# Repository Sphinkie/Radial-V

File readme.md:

# Radial-V

## Présentation

Remise en fonctionnement d'un poste de TSF, avec radio FM, player MP3, et afficheur LCD.

## Fabrication

Plusieurs éléments ont été réalisés: logiciel, circuits électroniques et supports en PLA.

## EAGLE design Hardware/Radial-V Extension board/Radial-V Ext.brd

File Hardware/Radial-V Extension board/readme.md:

# RADIAL-V

## Extension Board

Cette carte regroupe tous les capteurs et actuateurs (boutons, LEDs, etc) du système et les envoie sur une nappe 25 fils vers l'Arduino.

Le circuit intégré 74HC14 est un *trigger de Schmitt inversé* qui, associé aux capacités, supprime les rebonds des boutons poussoirs, et transforme les impulsions en signaux carrés propres inversés (*active high*).  
Les *relais* servent à commuter le signal audio de sortie soit de la source "Carte MP3", soit de la source "Carte radio FM".  
Les composants *grisés* sont des spares non utilisés.

Schémas et PCB compatibles avec le logiciel **Eagle**.

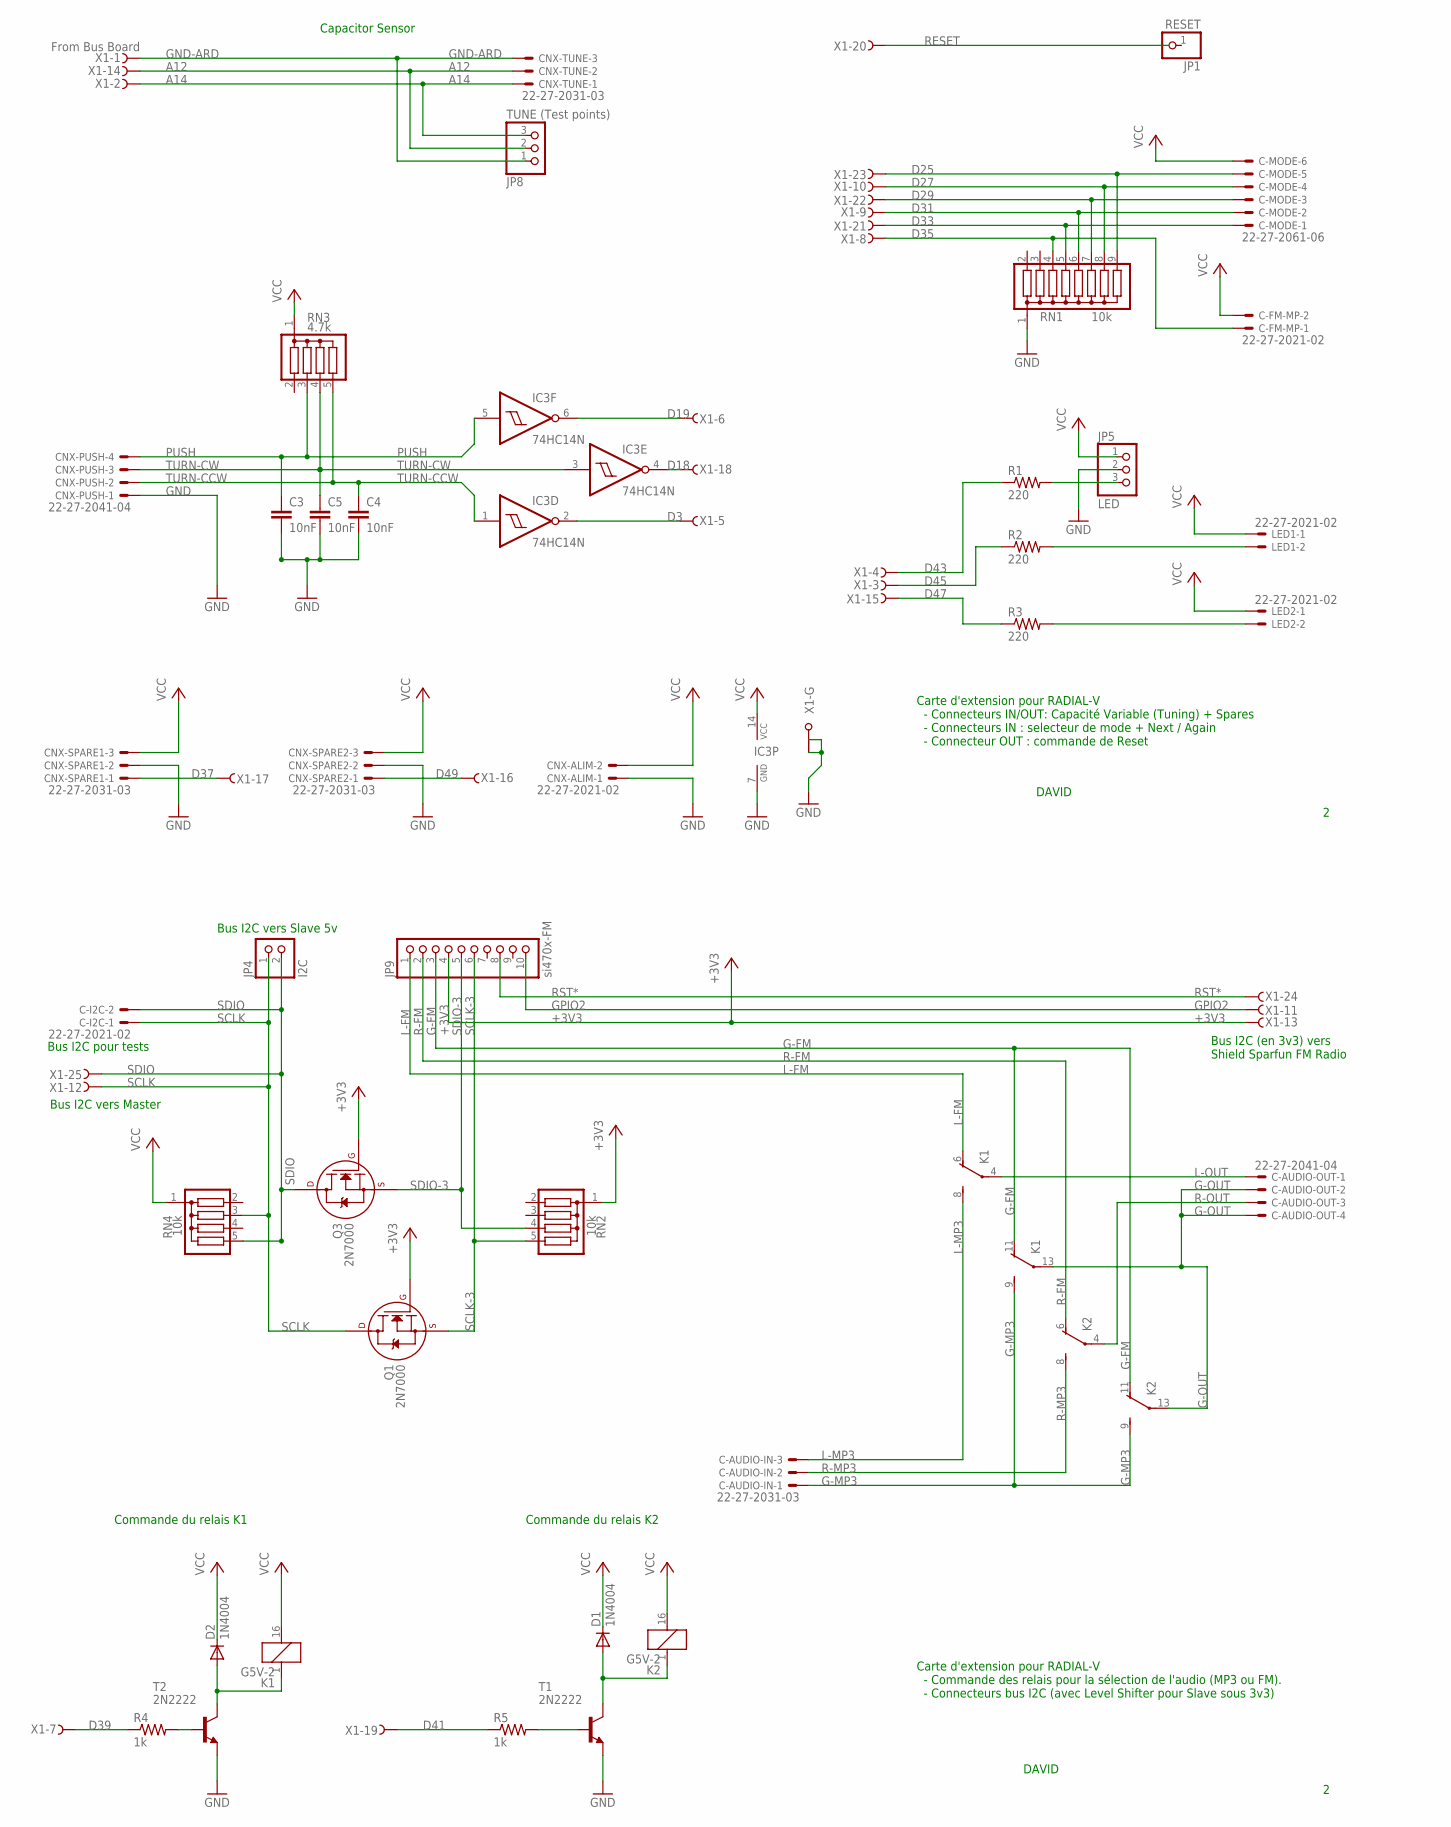
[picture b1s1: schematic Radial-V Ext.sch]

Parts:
C3, C4, C5: 10nF; C050-050X075
C-AUDIO-IN: 22-27-2031-03; 6410-03
C-AUDIO-OUT: 22-27-2041-04; 6410-04
C-FM-MP: 22-27-2021-02; 6410-02
C-I2C: 22-27-2021-02; 6410-02
C-MODE: 22-27-2061-06; 6410-06
CNX-ALIM: 22-27-2021-02; 6410-02
CNX-PUSH: 22-27-2041-04; 6410-04
CNX-SPARE1, CNX-SPARE2: 22-27-2031-03; 6410-03
CNX-TUNE: 22-27-2031-03; 6410-03
D1, D2: 1N4004; DO41-10
IC3: 74HC14N; DIL14
JP1: RESET; 1X01
JP4: I2C; 1X02
JP5: LED; 1X03
JP8: TUNE (Test points); 1X03
JP9: si470x-FM; 1X10
K1, K2: G5V-2
LED1, LED2: 22-27-2021-02; 6410-02
Q1, Q3: 2N7000; TO-92
R1, R2, R3: 220; 0411/15
R4, R5: 1k; 0411/15
RN1: 10k; SIL9
RN2, RN4: 10k; SIL5
RN3: 4.7k; SIL5
T1, T2: 2N2222; TO18
X1: From Bus Board; F25HP

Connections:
+3V3: JP9.4, Q1.2 (G), Q3.2 (G), RN2.1, X1.13 (F)
A12: CNX-TUNE.2, JP8.2, X1.14 (F)
A14: CNX-TUNE.1, JP8.3, X1.2 (F)
D3: IC3.2 (O), X1.5 (F)
D18: IC3.4 (O), X1.18 (F)
D19: IC3.6 (O), X1.6 (F)
D25: C-MODE.5, RN1.9, X1.23 (F)
D27: C-MODE.4, RN1.8, X1.10 (F)
D29: C-MODE.3, RN1.7, X1.22 (F)
D31: C-MODE.2, RN1.6, X1.9 (F)
D33: C-MODE.1, RN1.5, X1.21 (F)
D35: C-FM-MP.1, RN1.4, X1.8 (F)
D37: CNX-SPARE1.1, X1.17 (F)
D39: R4.1, X1.7 (F)
D41: R5.1, X1.19 (F)
D43: R1.1, X1.4 (F)
D45: R2.1, X1.3 (F)
D47: R3.1, X1.15 (F)
D49: CNX-SPARE2.1, X1.16 (F)
G-FM: JP9.3, K1.11 (O), K2.11 (O)
G-MP3: C-AUDIO-IN.1, K1.9 (S), K2.9 (S)
G-OUT: C-AUDIO-OUT.2, C-AUDIO-OUT.4, K1.13, K2.13
GND: C3.2, C4.2, C5.2, CNX-ALIM.1, CNX-PUSH.1, CNX-SPARE1.2, CNX-SPARE2.2, IC3.7 (GND), JP5.2, RN1.1, T1.1 (E), T2.1 (E), X1.G1, X1.G2
GND-ARD: CNX-TUNE.3, JP8.1, X1.1 (F)
GPIO2: JP9.10, X1.11 (F)
L-FM: JP9.1, K1.6 (O)
L-MP3: C-AUDIO-IN.3, K1.8 (S)
L-OUT: C-AUDIO-OUT.1, K1.4
unnamed: D2.A, K1.1, T2.3 (C)
unnamed: LED1.2, R2.2
unnamed: D1.A, K2.1, T1.3 (C)
unnamed: JP5.3, R1.2
unnamed: LED2.2, R3.2
unnamed: R4.2, T2.2 (B)
unnamed: R5.2, T1.2 (B)
PUSH: C3.1, CNX-PUSH.4, IC3.5 (I), RN3.3
R-FM: JP9.2, K2.6 (O)
R-MP3: C-AUDIO-IN.2, K2.8 (S)
R-OUT: C-AUDIO-OUT.3, K2.4
RESET: X1.20 (F)
RST*: JP9.8, X1.24 (F)
SCLK: C-I2C.1, JP4.1, Q1.3 (D), RN4.3, X1.12 (F)
SCLK-3: JP9.6, Q1.1 (S), RN2.5
SDIO: C-I2C.2, JP4.2, Q3.3 (D), RN4.5, X1.25 (F)
SDIO-3: JP9.5, Q3.1 (S), RN2.4
TURN-CCW: C4.1, CNX-PUSH.2, IC3.1 (I), RN3.5
TURN-CW: C5.1, CNX-PUSH.3, IC3.3 (I), RN3.4
VCC: C-FM-MP.2, C-MODE.6, CNX-ALIM.2, CNX-SPARE1.3, CNX-SPARE2.3, D1.C, D2.C, IC3.14 (VCC), JP5.1, K1.16 (2), K2.16 (2), LED1.1, LED2.1, RN3.1, RN4.1

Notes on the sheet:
Capacitor Sensor
DAVID
Carte d'extension pour RADIAL-V - Connecteurs IN/OUT: Capacité Variable (Tuning) + Spares - Connecteurs IN : selecteur de mode + Next / Again - Connecteur OUT : commande de Reset
Commande du relais K1
Commande du relais K2
Bus I2C vers Slave 5v
Bus I2C (en 3v3) vers Shield Sparfun FM Radio
Bus I2C vers Master
Bus I2C pour tests
Carte d'extension pour RADIAL-V - Commande des relais pour la sélection de l'audio (MP3 ou FM). - Connecteurs bus I2C (avec Level Shifter pour Slave sous 3v3)

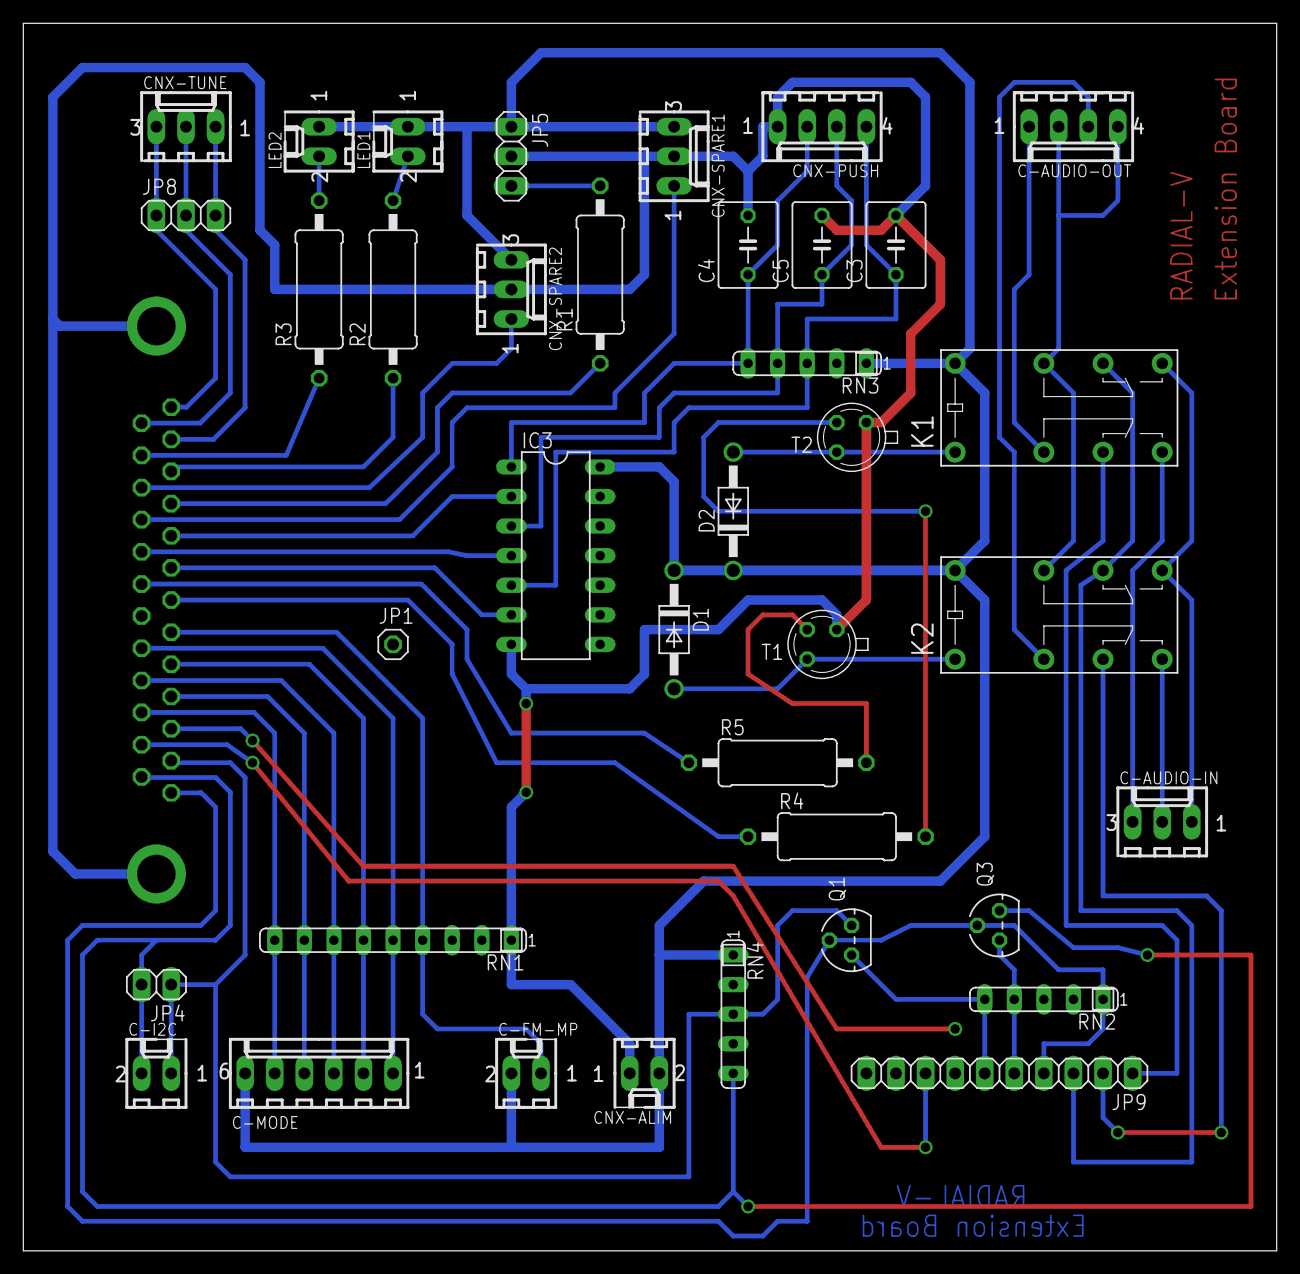
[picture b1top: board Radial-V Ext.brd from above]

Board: 2 copper layers, 107.6 x 105.4 mm, 39 parts (1 on the bottom side), 47 nets.

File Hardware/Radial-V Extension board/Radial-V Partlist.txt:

Partlist

Exported from Radial-V Ext.sch at 27/12/2015 20:11

EAGLE Version 7.4.0 Copyright (c) 1988-2015 CadSoft

Assembly variant: 

Part        Value          Device          Package      Library      Sheet

C-AUDIO-IN  22-27-2031-03  22-27-2031-03   6410-03      con-molex    1
C-AUDIO-OUT 22-27-2041-04  22-27-2041-04   6410-04      con-molex    1
C-FM-MP     22-27-2021-02  22-27-2021-02   6410-02      con-molex    1
C-I2C       22-27-2021-02  22-27-2021-02   6410-02      con-molex    1
C-MODE      22-27-2061-06  22-27-2061-06   6410-06      con-molex    1
C3          10nF           C-EU050-050X075 C050-050X075 rcl          1
C4          10nF           C-EU050-050X075 C050-050X075 rcl          1
C5          10nF           C-EU050-050X075 C050-050X075 rcl          1
CNX-ALIM    22-27-2021-02  22-27-2021-02   6410-02      con-molex    1
CNX-PUSH    22-27-2041-04  22-27-2041-04   6410-04      con-molex    1
CNX-SPARE   22-27-2031-03  22-27-2031-03   6410-03      con-molex    1
CNX-SPI     22-27-2031-03  22-27-2031-03   6410-03      con-molex    1
CNX-TUNE    22-27-2031-03  22-27-2031-03   6410-03      con-molex    1
D1          1N4004         1N4004          DO41-10      diode        1
D2          1N4004         1N4004          DO41-10      diode        1
IC3         74HC14N        74HC14N         DIL14        74xx-eu      1
JP4         I2C            PINHD-1X2       1X02         pinhead      1
JP5         LED            PINHD-1X3       1X03         pinhead      1
JP8         SPI            PINHD-1X3       1X03         pinhead      1
JP9         si470x-FM      PINHD-1X10      1X10         pinhead      1
K1          G5V-2          G5V-2           G5V-2        relay        1
K2          G5V-2          G5V-2           G5V-2        relay        1
LED1        22-27-2021-02  22-27-2021-02   6410-02      con-molex    1
LED2        22-27-2021-02  22-27-2021-02   6410-02      con-molex    1
Q1          2N7000         2N7000_TO92     TO-92        transistors  1
Q3          2N7000         2N7000_TO92     TO-92        transistors  1
R1          220            R-US_0411/15    0411/15      rcl          1
R2          220            R-US_0411/15    0411/15      rcl          1
R3          220            R-US_0411/15    0411/15      rcl          1
R4          1k             R-US_0411/15    0411/15      rcl          1
R5          1k             R-US_0411/15    0411/15      rcl          1
RN1         10k            G08R            SIL9         resistor-sil 1
RN2         10k            G04R            SIL5         resistor-sil 1
RN3         4.7k           G04R            SIL5         resistor-sil 1
RN4         10k            G04R            SIL5         resistor-sil 1
T1          2N2222         2N2222          TO18         transistor   1
T2          2N2222         2N2222          TO18         transistor   1
X1          ARDUINO        F25HPS          F25HP        con-subd     1

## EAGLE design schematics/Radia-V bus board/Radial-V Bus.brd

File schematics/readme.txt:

To generate the file for JLB PCB:

kiCad → Pcbnew → File → Plot...
  Plot format: Gerber
  Output directory: Gerber\
  Included layers: F.Cu B.Cu F.SilkS B.SilkS F.Mask B.Mask Edge.Cuts
  Plot footprint values
  Plot footprint references
  Exclude PDB edge layer from other layers
  Exclude pads from silkscreen

Plot

Generate Drill Files...
Generate Drill Files

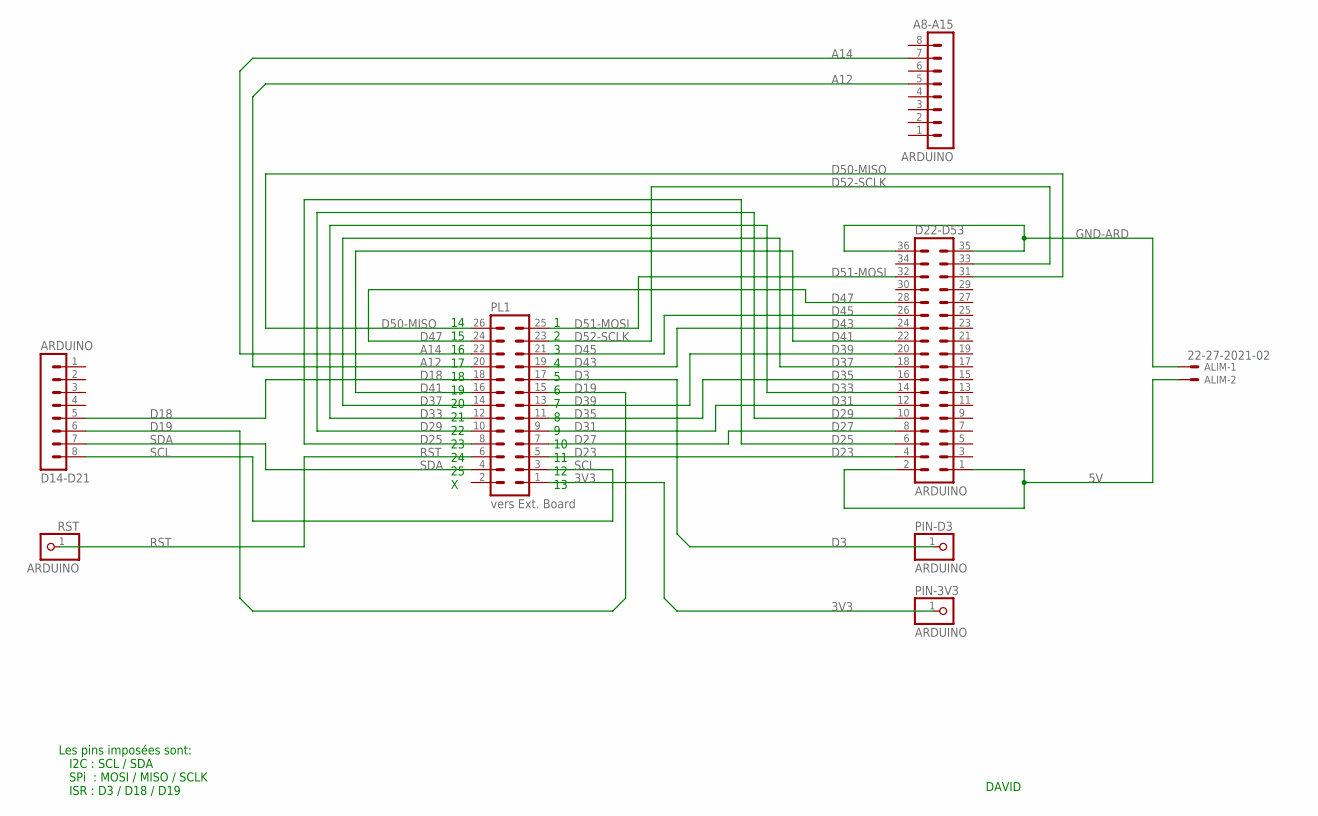
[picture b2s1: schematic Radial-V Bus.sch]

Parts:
A8-A15: ARDUINO; MA08-1
ALIM: 22-27-2021-02; 6410-02
D14-D21: ARDUINO; MA08-1
D22-D53: ARDUINO; MA18-2
PIN-3V3: ARDUINO; 1X01
PIN-D3: ARDUINO; 1X01
PL1: vers Ext. Board; 26H
RST: ARDUINO; 1X01

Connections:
3V3: PIN-3V3.1, PL1.1
5V: ALIM.2, D22-D53.1, D22-D53.2
A12: A8-A15.5, PL1.20
A14: A8-A15.7, PL1.22
D3: PIN-D3.1, PL1.17
D18: D14-D21.5, PL1.18
D19: D14-D21.6, PL1.15
D23: D22-D53.4, PL1.5
D25: D22-D53.6, PL1.8
D27: D22-D53.8, PL1.7
D29: D22-D53.10, PL1.10
D31: D22-D53.12, PL1.9
D33: D22-D53.14, PL1.12
D35: D22-D53.16, PL1.11
D37: D22-D53.18, PL1.14
D39: D22-D53.20, PL1.13
D41: D22-D53.22, PL1.16
D43: D22-D53.24, PL1.19
D45: D22-D53.26, PL1.21
D47: D22-D53.28, PL1.24
D50-MISO: D22-D53.31, PL1.26
D51-MOSI: D22-D53.32, PL1.25
D52-SCLK: D22-D53.33, PL1.23
GND-ARD: ALIM.1, D22-D53.35, D22-D53.36
RST: PL1.6, RST.1
SCL: D14-D21.8, PL1.3
SDA: D14-D21.7, PL1.4

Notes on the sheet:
14 15 16 17 18 19 20 21 22 23 24 25 X
Les pins imposées sont: I2C : SCL / SDA SPi : MOSI / MISO / SCLK ISR : D3 / D18 / D19
DAVID
1 2 3 4 5 6 7 8 9 10 11 12 13

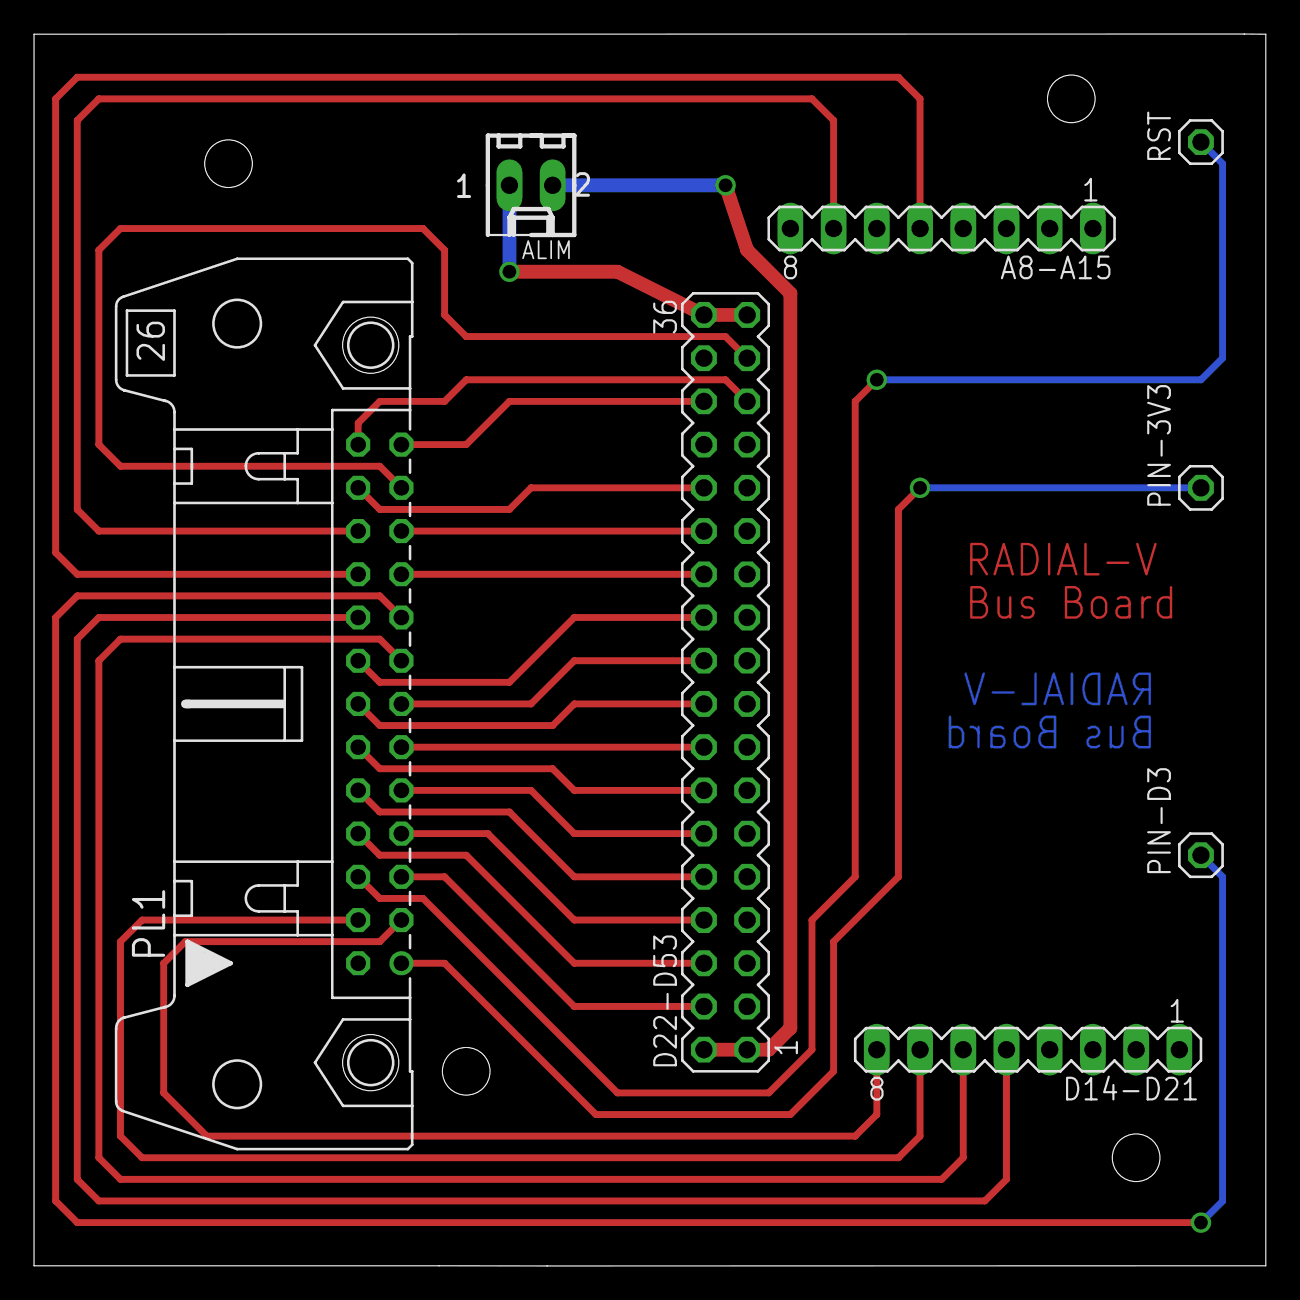
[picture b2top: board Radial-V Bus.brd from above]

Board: 2 copper layers, 72.4 x 72.4 mm, 8 parts (0 on the bottom side), 27 nets.

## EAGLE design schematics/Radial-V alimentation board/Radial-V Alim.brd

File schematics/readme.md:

# RADIAL-V
## Schematics

Ce repository contient l'ingénérie des différents circuits imprimés réalisés.

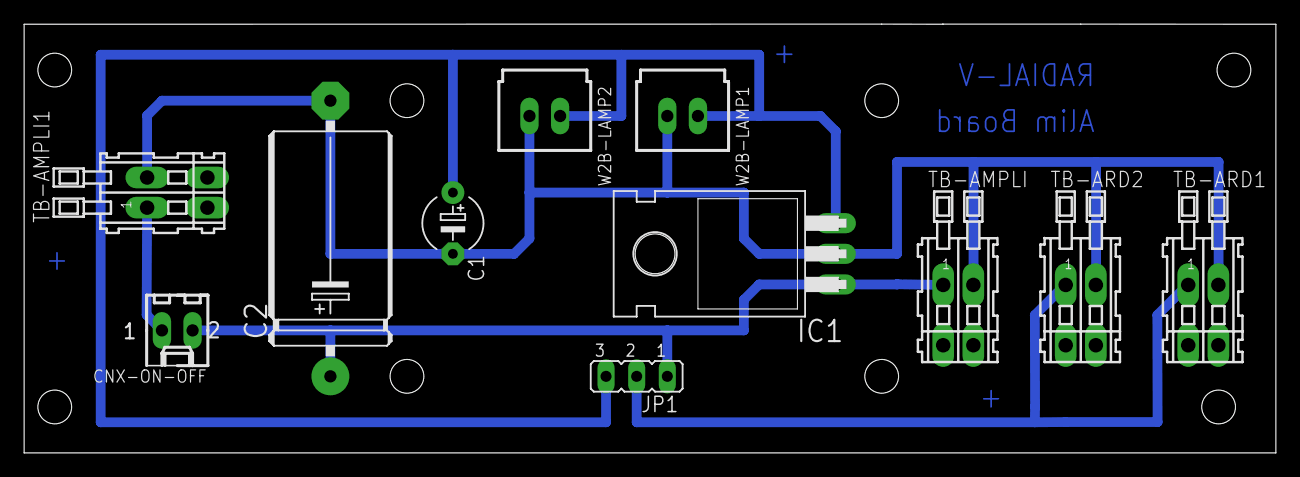
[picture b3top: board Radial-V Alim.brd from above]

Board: 2 copper layers, 103.8 x 35.6 mm, 11 parts (0 on the bottom side), 5 nets.

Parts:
C1: 10uF; E5-5
C2: 100uF; E22-10
CNX-ON-OFF: 22-27-2021-02; 6410-02
IC1: 7805T; TO220H
JP1: Jumper; JP2
TB-AMPLI: Wago234; 234-202
TB-AMPLI1: POWER-IN; 234-202
TB-ARD1, TB-ARD2: Wago234; 234-202
W2B-LAMP1, W2B-LAMP2: C-GRID-02-70543; 70543-02

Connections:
+5V: C1.+, IC1.3, JP1.3, W2B-LAMP1.1, W2B-LAMP2.1
GND: C1.-, C2.-, IC1.2, TB-AMPLI.A2, TB-AMPLI1.A2, TB-ARD1.A2, TB-ARD2.A2, W2B-LAMP1.2, W2B-LAMP2.2
unnamed: JP1.2, TB-ARD1.A1, TB-ARD2.A1
unnamed: CNX-ON-OFF.1, TB-AMPLI1.A1
VCC: C2.+, CNX-ON-OFF.2, IC1.1, JP1.1, TB-AMPLI.A1

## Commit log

2018-01-25 :tada: Added .gitattributes
2018-01-25 schematics
2019-12-28 3D view des cartes
2019-12-29 Add docs for Spackfun FM card
2019-12-30 Wait for I2C Slave + Unicode converter
2019-12-31 Gestion des accents
2020-01-01 Recabling C-MODE connector
2020-01-01 Title on 2 lines
2020-01-02 Changement de de cablage
2020-01-02 Gestion du titre déroulant
2020-01-11 Affichage du Mode en rouge
2020-01-11 Adding STL files (3D printed objects)
2020-01-11 3D objects updated
2020-01-12 Meilleur rafraichissement du Rating affiché
2020-01-12 no backlight for FM
2020-01-19 Implémentation de la library pour shield FM Si7403
2020-01-20 Bus board recreated with Kicad
2020-01-21 Update Bus Board
2020-01-21 Routage Bus Board
2020-01-22 Bus Board
2020-01-26 Ajout de Radio Board
2020-01-26 wire fix
2020-01-26 Regroupement de A12 et A14 sur le même connecteur
2020-01-26 Header ARD-J4 mis sur la couche Bottom
2020-01-26 Mise à jour du mapping des I/O dans Extension Board
2020-01-26 Generation des fichiers Gerber
2020-01-26 Add readme
2020-01-26 change filenames
2020-01-26 Add a Readme for Bus Board
2020-01-26 Arduino LCD screen documentation
2020-01-28 Actualisation de documentation
2020-01-29 Mise à jour des Readme
2020-01-30 mise à jour des images
2020-02-01 change case of directory
2020-02-01 Ajout de nouvelles images
2020-02-05 3D models added
2020-02-06 Update Audio Board
2020-02-07 Add PreAmplifier Board
2020-02-07 Add Amplfier board
2020-02-09 Velleman Amplifier Board
2020-02-09 STL models added
2020-02-09 STL model added
2020-02-09 Adding preamplifier 3D model
2020-02-16 Audio support 3D model
2020-02-16 fichiers remis dans le bon repertoire...
2020-02-20 Updated models
2020-02-23 Remmaping des E/S après installation BusBoard V2
2020-02-23 Essai de vérification si Arduino Slave present
    Peut être utile car la librarie WIRE se bloque s'il n'y a pas de Slave I2C.
2020-02-24 Aout de la possibilité de tester avec Arduino 2 deconnecté
2020-03-02 Calibrage de la Capa Variable (in progress)
2020-03-04 Mersure de la Capa
    par une meilleure méthode
2020-03-05 Etalonnage des mesures de la capa
2020-03-06 Mesure stabilisée de la capa : OK
2020-03-07 cleanup code
2020-03-09 updated component view
2020-03-09 Updated picture size
2020-03-10 Fichier readme
2020-03-10 readme
2020-03-23 with comments
2020-03-24 documentation
2020-04-10 Include Si4703 FM shield library
2020-04-10 Testing FM player (wip)
2020-04-10 There are I2C NACK errors
2020-04-13 Le code pour la FM est en place: masi ABANDON
    Abandon de la foncrtionnalité FM, car impossible de communiquer avec la carte Si4703.
    La librairie reste en place, ainsi de futures tentatives restent possibles...
2020-04-16 Tests unitaires de la carte FM.
    NACK si on met des adaptations de tension.
    OK si on ne met aucune adaptation...
    génial....
2020-04-16 Adjust Si4703 demo
2020-04-18 VERSION 2.3 - ABANDON DE LA FM
2020-04-20 Adding Amplifier Shunt board
2020-05-01 Classe de base CatalogFile
2020-05-01 Nouvelle classe MEDIA
2020-05-01 Reorganisation de la recherche (WIP)
2020-05-02 Reorganisation de la recherche (Done)
2020-05-09 New Catalog
2020-05-10 screenshots
2020-05-11 Patches pour VLSI
2020-05-16 Ajout des mini-cartes "Audio Adapter" et "Capa Adapter" et "PreAmp Shunt"
2020-05-17 Cleanup 3D models
2020-05-17 updated readme.md and pictures
2020-05-19 renommage de l'objet
2020-05-20 Pictures
2020-05-25 Détails du fichier Catalog
2020-08-01 update des tools
2020-10-15 Directory change
2020-10-15 Github web pages
2020-10-15 web pages
2020-10-15 Transparency
2022-03-31 update documentation
2022-04-03 Ajout KiCad Library: MesModules
2022-05-01 Project Githup Page
2022-05-02 détourage photos
2022-05-03 photo reworked
2024-02-11 Images et photos
    Détourage
2025-03-24 remove background
